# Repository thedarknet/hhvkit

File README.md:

hhvkit
======

DefCon 23 Hardware Hacking Village Learn To Solder Kit, by:
- Smitty, mark@halibut.com (concept, crypto, and firmware (2014))
- Krux, krux@thcnet.net (hardware)
- Cmdc0de, comc0dez@gmail.com (firmware (2015))

These are the files needed to build the firmware for the DefCon DarkNet
ID Badge that was sold as the Hardware Hacking Village's Learn To Solder
kit at DefCon 23 in 2015.

If you checkout the repo into your Arduino folder, it should just build
on Arduino v1.6.4.  

It creates the following directories:

DCDarkNet/Firmware/
- Contains the code.

DCDarkNet/Firmware/build/
- The automated build/burn system used to program over 300 chips in 
  just a couple hours. (ZIF socket not included. Some assembly required.)

libraries/IRSerial2014/
- A modified version of SoftwareSerial from Arduino 1.0 (don't know if 
  it's changed at all in 1.5) to allow for independent inverted logic
  on the Rx and Tx lines (so the idle state isn't HIGH on the IR LED
  and burn through battery), and to perform 38kHz modulation for the IR.

libraries/UsbKeyboard/
- A version of vusb-for-arduino [1] modified so it doesn't instantiate
  the USB object in the .h file and therefore immeidately upon startup.
  Instead, you instantiate the object whenever you want it and can
  delete it when you're done.
  [1] https://code.google.com/p/vusb-for-arduino/

libraries/DarkNetDisplay
- Modified version of the adafruit gfx and ssd_1306 libraries to work with our 
  darknet badge display
	https://github.com/adafruit/Adafruit-GFX-Library
	https://github.com/adafruit/Adafruit_SSD1306

Building and Burning
======

All the following commands are run inside DCDarkNet/Firmware/build/
This section is really only relevant if you are burning this code into
a whole bunch of chips.  If you're just burning your own chip, or are
playing around with different code, you're better off just using the 
Arduino IDE to program the board directly with an FTDI cable.

Preparation: GUIDs and private keys
======
The code is programmed to FLASH, but there are a few things needed in
EEPROM before the badge is functional.  If you have a chip from us, it
was already programmed with your GUID and private key, which will persist
through a re-flash.  But if you have a new chip, you'll need to program
your GUID and private key into the chip.

We don't currently (2015-08-2) have a way to generate new GUIDs and 
keys for you, nor to take in GUIDs and keys from you to put into the DB.
So you're welcome to play with this code and use it for other things, 
but unless you got a chip from us at DefCon, you won't be able to 
use your code on the live DarkNet site (https://dcdark.net.)

If you're building a whole new name space and don't need to interact 
with the DefCon DarkNet Daemon, you can generate your own DB of random
GUIDs and private keys using the build/buildDB.pl script, and redirecting
the output to a file called DB.  This doesn't actually do anything with 
the chip, it just generates random numbers and formats them correctly.

build$ ./buildDB.pl > DB

Preparation: Program
=======
All the source code is compiled down into a .hex file by Arduino. Those
who do more microcontroller work than I do can build this by hand.  I'm 
lazy and let Arduino do all the drudgery for me.

Go to preferences and enable "verbose output of the build process" or
whatever it's called.  This will make Arduino NOT delete the temporary
build directories it creates in /tmp.  Then build the code with Ctrl-R.
That will burn into /tmp/build[some number].tmp/   Find the most recent
build directory (the one that was likely just created or updated), and
copy Firmware.cpp.hex to your build/ directory:

build$ cp /tmp/build[some number].tmp/Firmware.cpp.hex .

You will have to do this EVERY TIME you build.

Burning Chips
=======
The burn-bootloader.sh script assumes you have a USBtinyISP [2].  You'll
need to modify the avr-dude command if you have a different ISP.
[2] http://www.adafruit.com/product/46

Connect the USBtinyISP to the ICSP header on your board and run:

build$ ./burn-bootloader.sh

Congrats!  Your badge is now an Arduino!  It can be programmed through
the FTDI header as if it were an Uno.

But to make it a DarkNet ID Badge, it needs the GUID and private key in 
EEPROM, and the program in flash.

The burn-eeprom.sh script takes a GUID on the command line, pulls it 
and it's associated key from the "DB" file generated above, formats
them into a .hex file that avr-dude can burn to EEPROM, and burns it.
Again, you'll need the USBtinyISP plugged into the ICSP header:

build$ ./burn-eeprom.sh GUIDGUID

After those two are done, the program can be written to flash using
the FTDI serial console cable (it's much faster than using the ICSP.)
burn-flash.sh takes the local file Firmware.cpp.hex you copied 
above.

build$ ./burn-flash.sh

Automating the Build
======
I wasn't about to run these three commands manually for 350 chips, so 
I wrote run.pl which pulls all the GUIDs from DB and cycles through 
them.  If all is happy and working, you can just run.pl, hit enter to
program a chip, swap the chip in the programming rig, hit enter again, 
lather, rinse, repeat.  It takes care of all the iteration on GUID,
as well as allows you to <N>ext and <P>rev through the DB list in case
a burn goes awry and needs to be redone.

build$ ./run.pl

BOM and Assembly Instructions
======

The Bill of Materials is located here:

https://www.mouser.com/ProjectManager/ProjectDetail.aspx?AccessID=6bc2d848d8

Assembly Instructions are located here:

- https://dcdark.net/2015/hhv-badge/
- https://dcdark.net/2015/hhv-display/

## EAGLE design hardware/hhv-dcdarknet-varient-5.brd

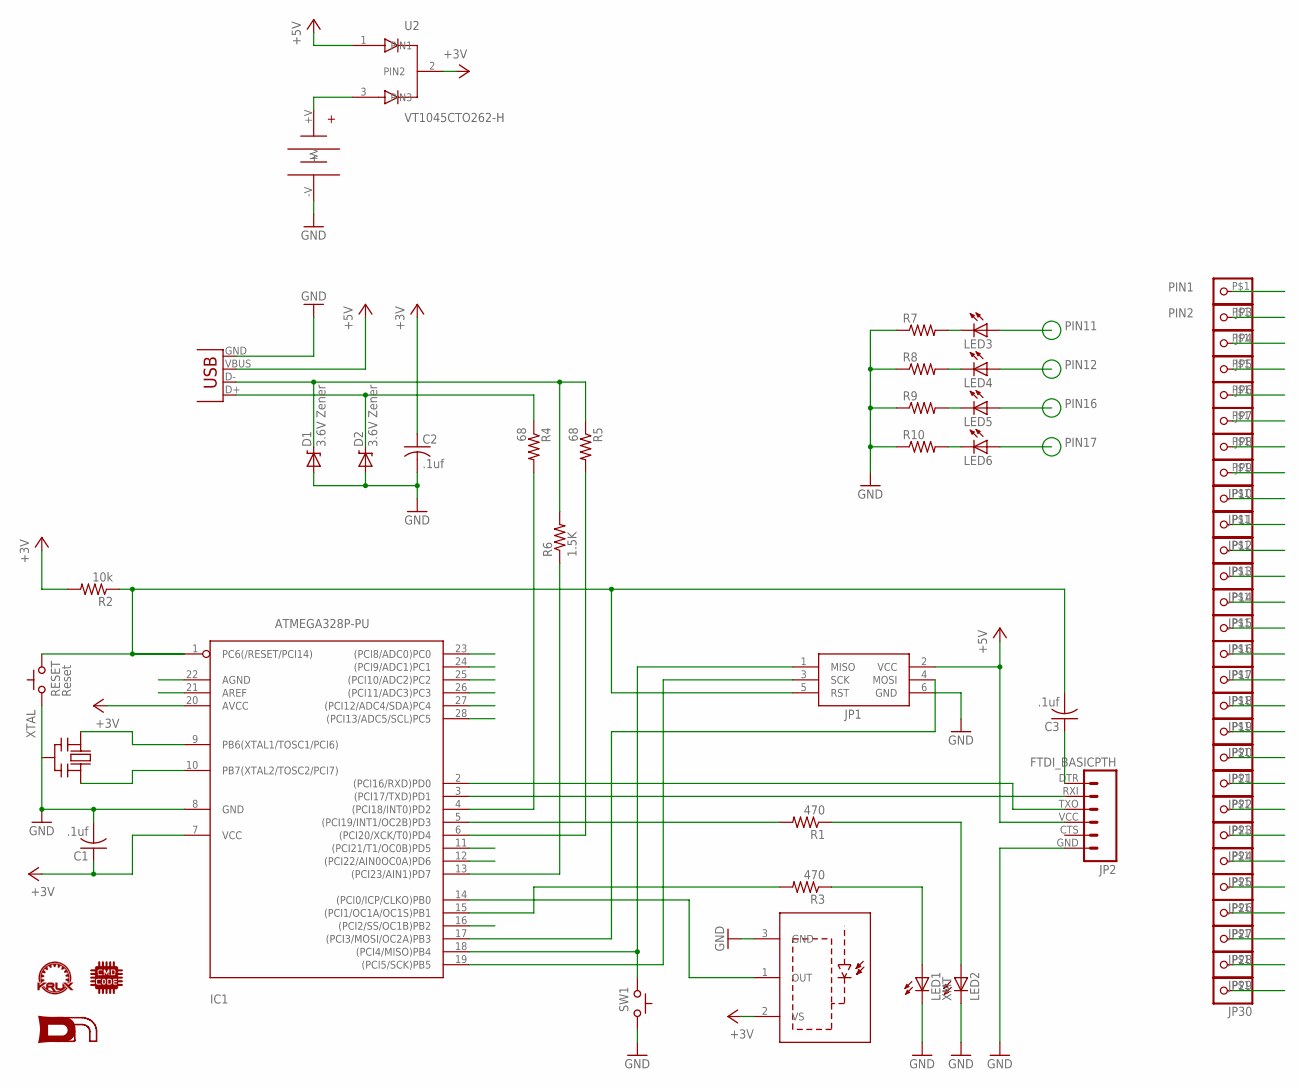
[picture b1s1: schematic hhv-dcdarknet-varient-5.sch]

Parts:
C1, C2, C3: .1uf; C025-030X050
D1, D2: 3.6V Zener; DIODE-ZENER
IC1: ATMEGA328P-PU; DIL28-3
JP1: JP1; AVRISP
JP2: FTDI_BASICPTH; FTDI_BASIC
JP3, JP4, JP5, JP6, JP7, JP8, JP9, JP10, JP11, JP12, JP13, JP14, JP15, JP16, JP17, JP18, JP19, JP20, JP21, JP22, JP23, JP24, JP25: PINHD-1X11X1_SQUARE; 1X1-SMALL_CUT
JP26, JP27, JP28, JP29, JP30: PINHD-1X11X1-SMALL; 1X1-SMALL
LED1: XMT; LED5MM-FLAT
LED2: LED5MM-FLAT
LED3, LED4, LED5, LED6: LED1206; LED-1206
R1, R3: 470; AXIAL-0.3
R2: 10k; AXIAL-0.3
R4, R5: 68; AXIAL-0.3
R6: 1.5K; AXIAL-0.3
R7, R8, R9, R10: RESISTOR1206; 1206
RESET: Reset; TACTILE-2PIN
SW1: SWITCH_TACTILETACTILE-2PIN; TACTILE-2PIN
U1: RCV; IR-MODULE
U2: VT1045CTO262-H; TO262-H
U$1: DN_LOGO
U$2: CMDC0DE_LOGO; CMDC0DE
U$3: KRUX_LOGO
U$5: 12BH423-GR3-CELL_NOBORDER; 3-AAA-CELL_NOBORDER
X2: USB; USB-B-PTH
XTAL: CERMOSCILL-THM; CERM_OSC

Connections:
+3V3: C1.1, C2.1, IC1.7 (VCC), IC1.20 (AVCC), JP9.P$1, JP22.P$1, R2.P$2 (2), U1.2 (VS), U2.2 (PIN2)
+5V: JP1.2 (VCC), JP2.VCC (4), U2.1 (PIN1), X2.VBUS
GND: C1.2, C2.2, D1.P$2 (A), D2.P$2 (A), IC1.8 (GND), JP1.6 (GND), JP2.GND (6), JP10.P$1, LED1.K (C), LED2.K (C), R7.1, R8.1, R9.1, R10.1, RESET.P$2 (C), SW1.P$1 (A), U1.3 (GND), U$5.-V, X2.GND, XTAL.P$2 (GND)
unnamed: C3.1, JP2.DTR (1)
unnamed: LED3.C, R7.2
unnamed: LED4.C, R8.2
unnamed: LED5.C, R9.2
unnamed: LED6.C, R10.2
unnamed: LED1.A, R3.P$1 (1)
unnamed: LED2.A, R1.P$1 (1)
unnamed: D2.P$1 (C), R4.P$1 (1), X2.D+
unnamed: U2.3 (PIN3), U$5.+V
PIN1: C3.2, IC1.1 (PC6(/RESET/PCI14)), JP1.5 (RST), JP3.P$1, R2.P$1 (1), RESET.P$1 (A)
PIN2: IC1.2 ((PCI16/RXD)PD0), JP2.TXO (3), JP4.P$1
PIN3: IC1.3 ((PCI17/TXD)PD1), JP2.RXI (2), JP5.P$1
PIN4: IC1.4 ((PCI18/INT0)PD2), JP6.P$1, R4.P$2 (2)
PIN5: IC1.5 ((PCI19/INT1/OC2B)PD3), JP7.P$1, R1.P$2 (2)
PIN6: IC1.6 ((PCI20/XCK/T0)PD4), JP8.P$1, R5.P$2 (2)
PIN9: IC1.9 (PB6(XTAL1/TOSC1/PCI6)), JP11.P$1, XTAL.P$1 (IN)
PIN10: IC1.10 (PB7(XTAL2/TOSC2/PCI7)), JP12.P$1, XTAL.P$3 (OUT)
PIN11: IC1.11 ((PCI21/T1/OC0B)PD5), JP13.P$1, LED3.A
PIN12: IC1.12 ((PCI22/AIN0OC0A)PD6), JP14.P$1, LED4.A
PIN13: IC1.13 ((PCI23/AIN1)PD7), JP15.P$1, R6.P$1 (1)
PIN14: IC1.14 ((PCI0/ICP/CLKO)PB0), JP16.P$1, U1.1 (OUT)
PIN15: IC1.15 ((PCI1/OC1A/OC1S)PB1), JP17.P$1, R3.P$2 (2)
PIN16: IC1.16 ((PCI2/SS/OC1B)PB2), JP18.P$1, LED5.A
PIN17: IC1.17 ((PCI3/MOSI/OC2A)PB3), JP1.4 (MOSI), JP19.P$1, LED6.A
PIN18: IC1.18 ((PCI4/MISO)PB4), JP1.1 (MISO), JP20.P$1, SW1.P$2 (C)
PIN19: IC1.19 ((PCI5/SCK)PB5), JP1.3 (SCK), JP21.P$1
PIN21: IC1.21 (AREF), JP23.P$1
PIN22: IC1.22 (AGND), JP24.P$1
PIN23: IC1.23 ((PCI8/ADC0)PC0), JP25.P$1
PIN24: IC1.24 ((PCI9/ADC1)PC1), JP26.P$1
PIN25: IC1.25 ((PCI10/ADC2)PC2), JP27.P$1
PIN26: IC1.26 ((PCI11/ADC3)PC3), JP28.P$1
PIN27: IC1.27 ((PCI12/ADC4/SDA)PC4), JP29.P$1
PIN28: IC1.28 ((PCI13/ADC5/SCL)PC5), JP30.P$1
USB: D1.P$1 (C), R5.P$1 (1), R6.P$2 (2), X2.D-

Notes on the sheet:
PIN11
PIN12
PIN16
PIN17

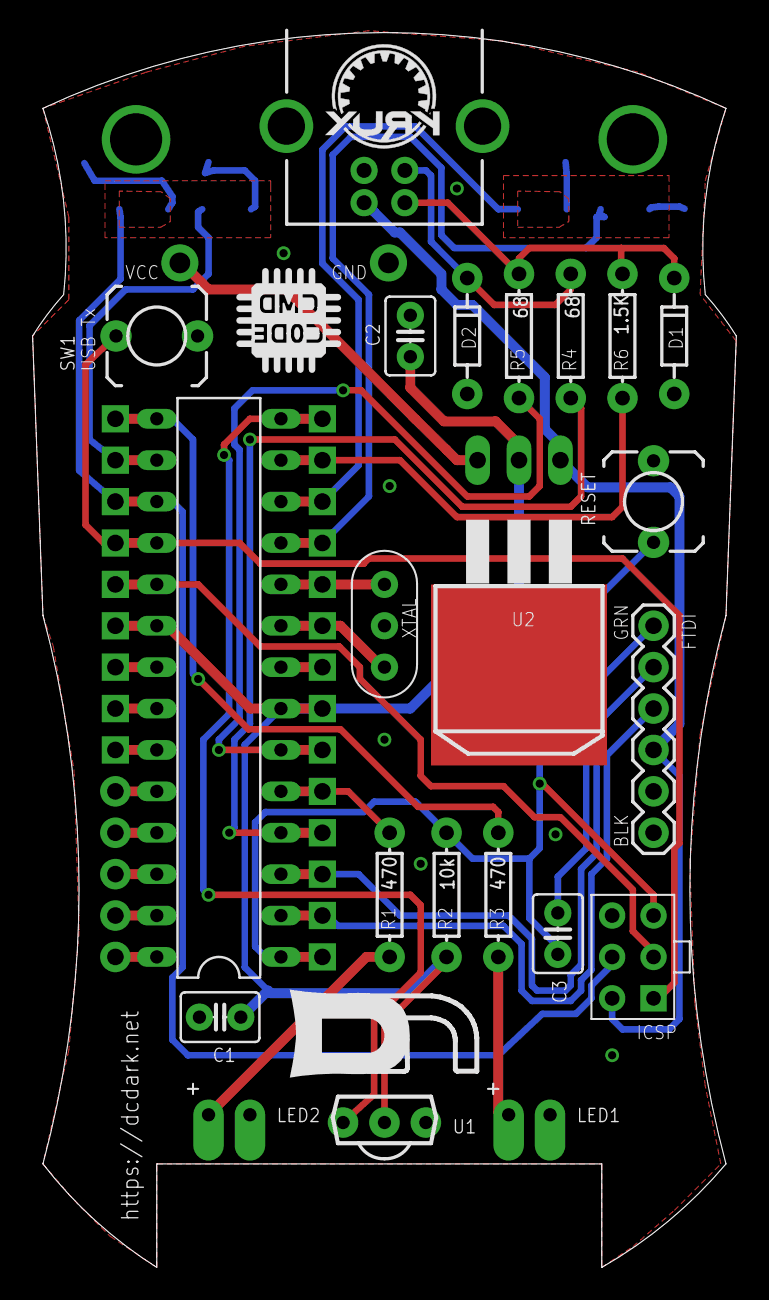
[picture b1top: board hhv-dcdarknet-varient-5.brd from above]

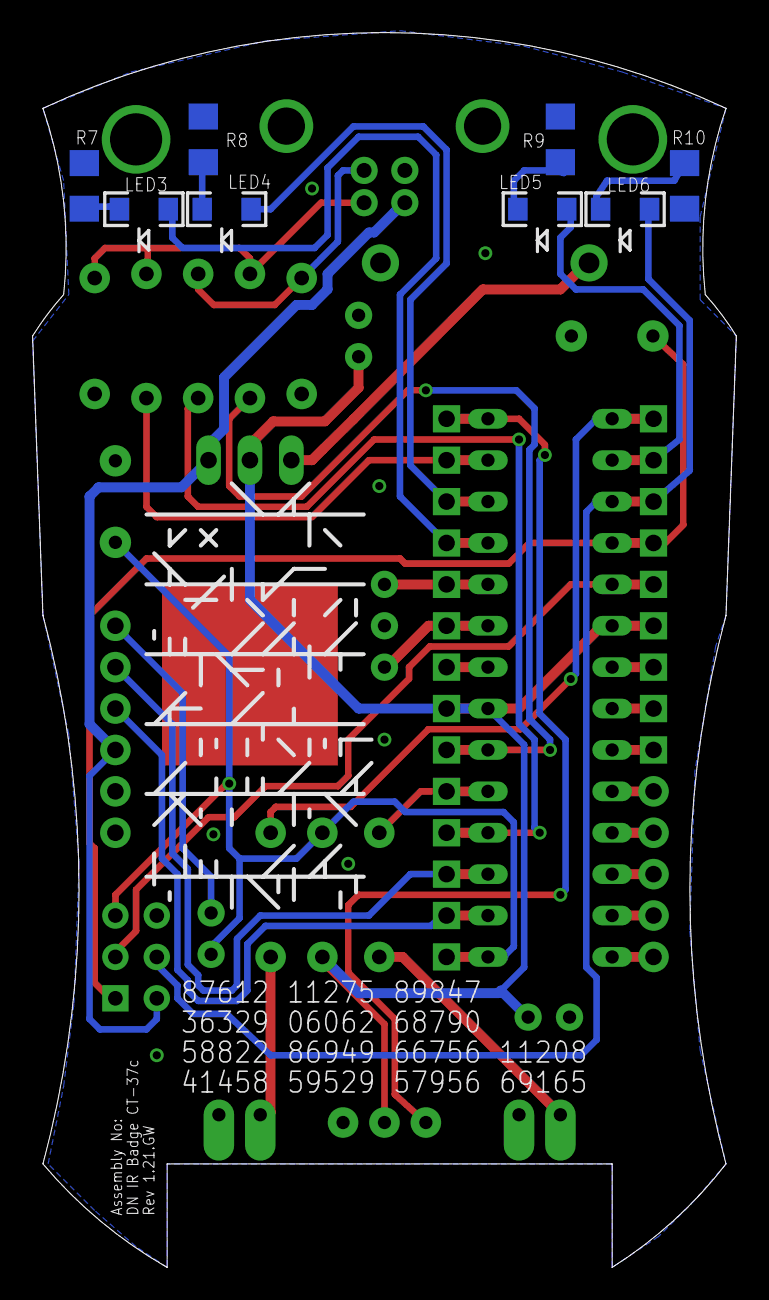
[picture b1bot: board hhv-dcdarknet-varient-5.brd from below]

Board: 2 copper layers, 43.2 x 75.8 mm, 62 parts (10 on the bottom side), 38 nets.

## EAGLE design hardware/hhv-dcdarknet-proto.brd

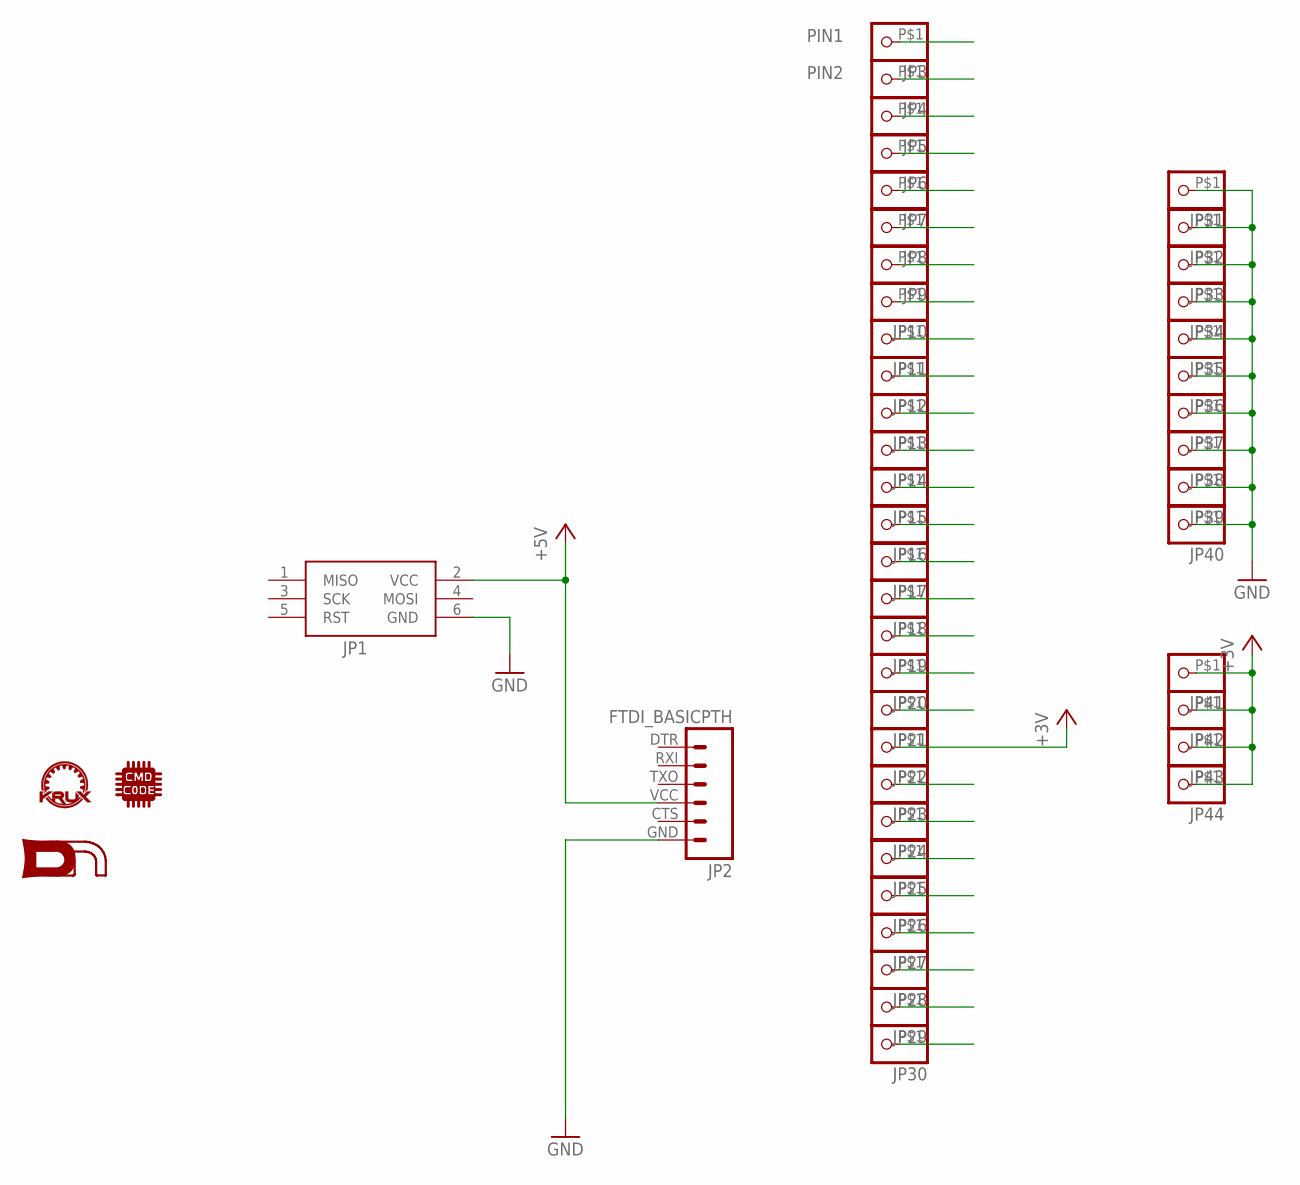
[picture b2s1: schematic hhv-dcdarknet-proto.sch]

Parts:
JP1: JP1; AVRISP
JP2: FTDI_BASICPTH; FTDI_BASIC
JP3, JP4, JP5, JP6, JP7, JP8, JP9, JP10, JP11, JP12, JP13, JP14, JP15, JP16, JP17, JP18, JP19, JP20, JP21, JP22, JP23, JP24, JP25, JP26, JP27, JP28, JP29, JP30, JP31, JP32, JP33, JP34, JP35, JP36, JP37, JP38, JP39, JP40, JP41, JP42, JP43, JP44: PINHD-1X11X1_SQUARE; 1X1-SMALL_CUT
U$1: KRUX_LOGO
U$2: DN_LOGO
U$3: CMDC0DE_LOGO; CMDC0DE

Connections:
+3V3: JP9.P$1, JP22.P$1, JP41.P$1, JP42.P$1, JP43.P$1, JP44.P$1
+5V: JP1.2 (VCC), JP2.VCC (4)
GND: JP1.6 (GND), JP2.GND (6), JP10.P$1, JP31.P$1, JP32.P$1, JP33.P$1, JP34.P$1, JP35.P$1, JP36.P$1, JP37.P$1, JP38.P$1, JP39.P$1, JP40.P$1
PIN1: JP3.P$1
PIN2: JP4.P$1
PIN3: JP5.P$1
PIN4: JP6.P$1
PIN5: JP7.P$1
PIN6: JP8.P$1
PIN9: JP11.P$1
PIN10: JP12.P$1
PIN11: JP13.P$1
PIN12: JP14.P$1
PIN13: JP15.P$1
PIN14: JP16.P$1
PIN15: JP17.P$1
PIN16: JP18.P$1
PIN17: JP19.P$1
PIN18: JP20.P$1
PIN19: JP21.P$1
PIN21: JP23.P$1
PIN22: JP24.P$1
PIN23: JP25.P$1
PIN24: JP26.P$1
PIN25: JP27.P$1
PIN26: JP28.P$1
PIN27: JP29.P$1
PIN28: JP30.P$1

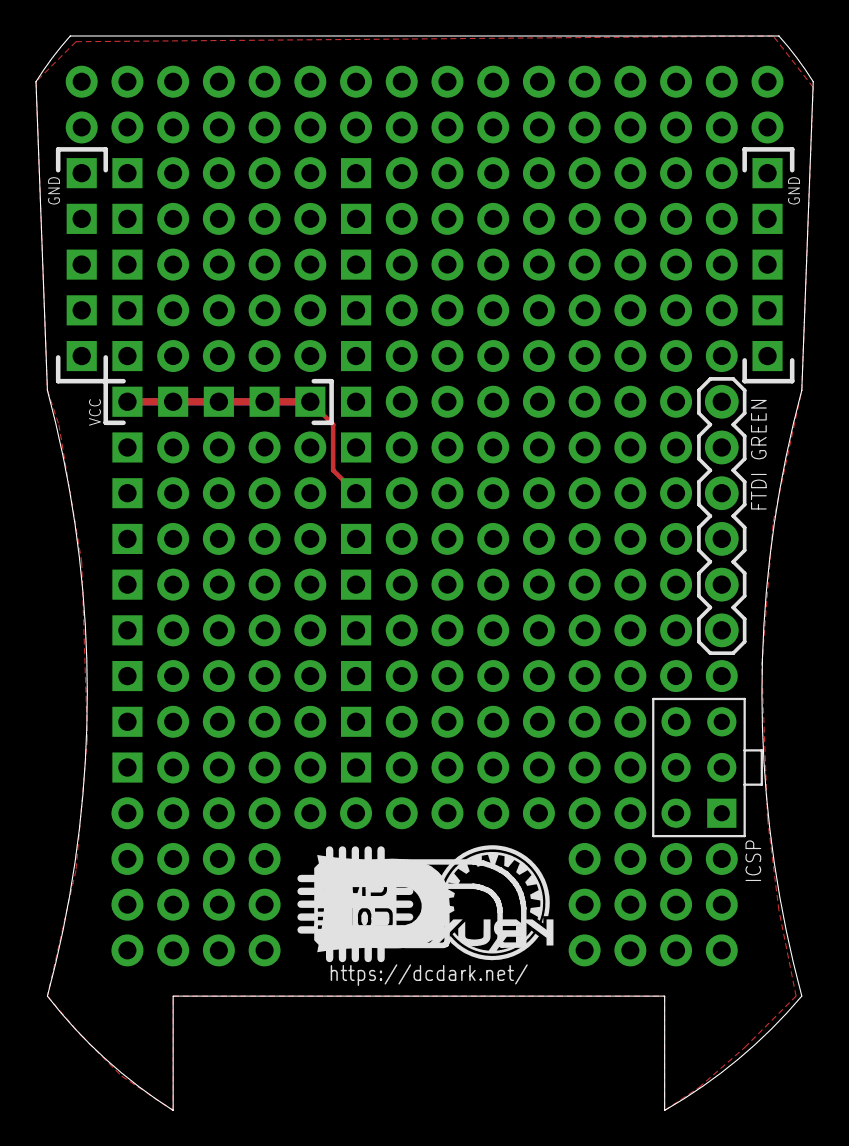
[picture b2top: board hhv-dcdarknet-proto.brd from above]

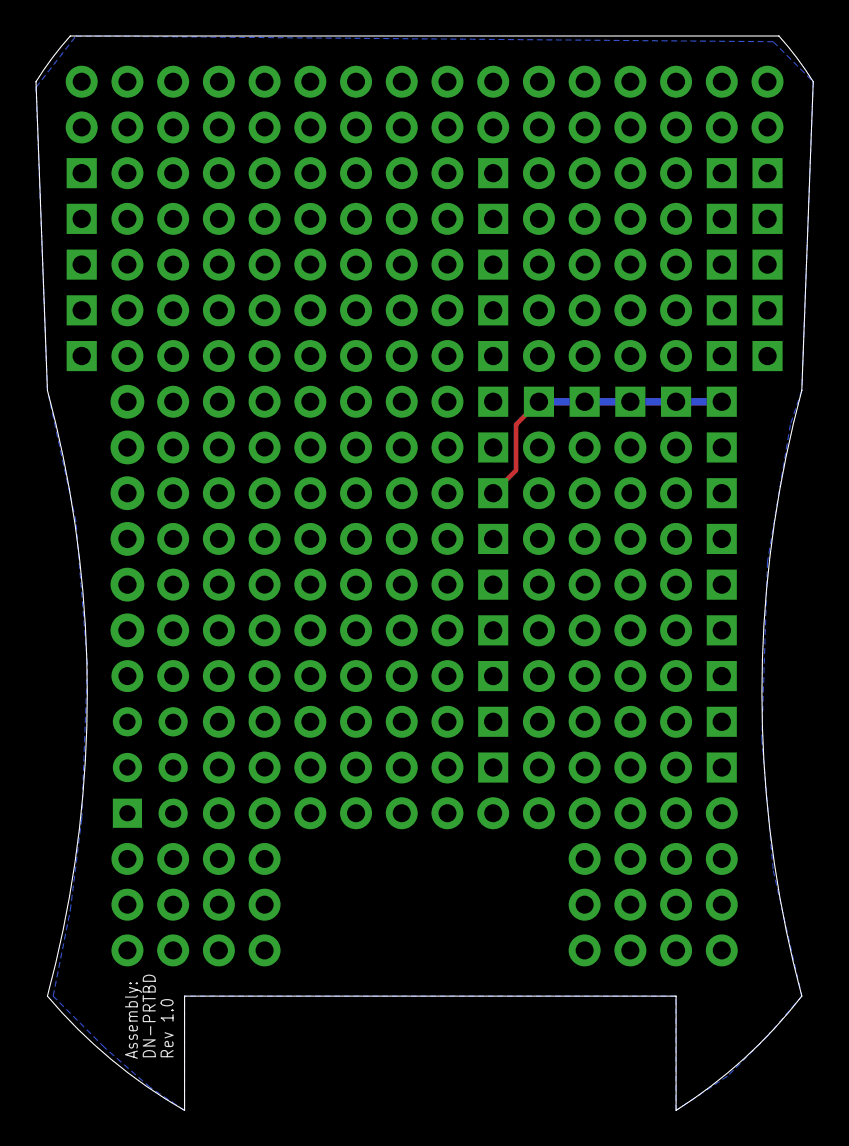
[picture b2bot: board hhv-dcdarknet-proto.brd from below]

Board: 2 copper layers, 43.2 x 59.7 mm, 47 parts (2 on the bottom side), 3 nets.

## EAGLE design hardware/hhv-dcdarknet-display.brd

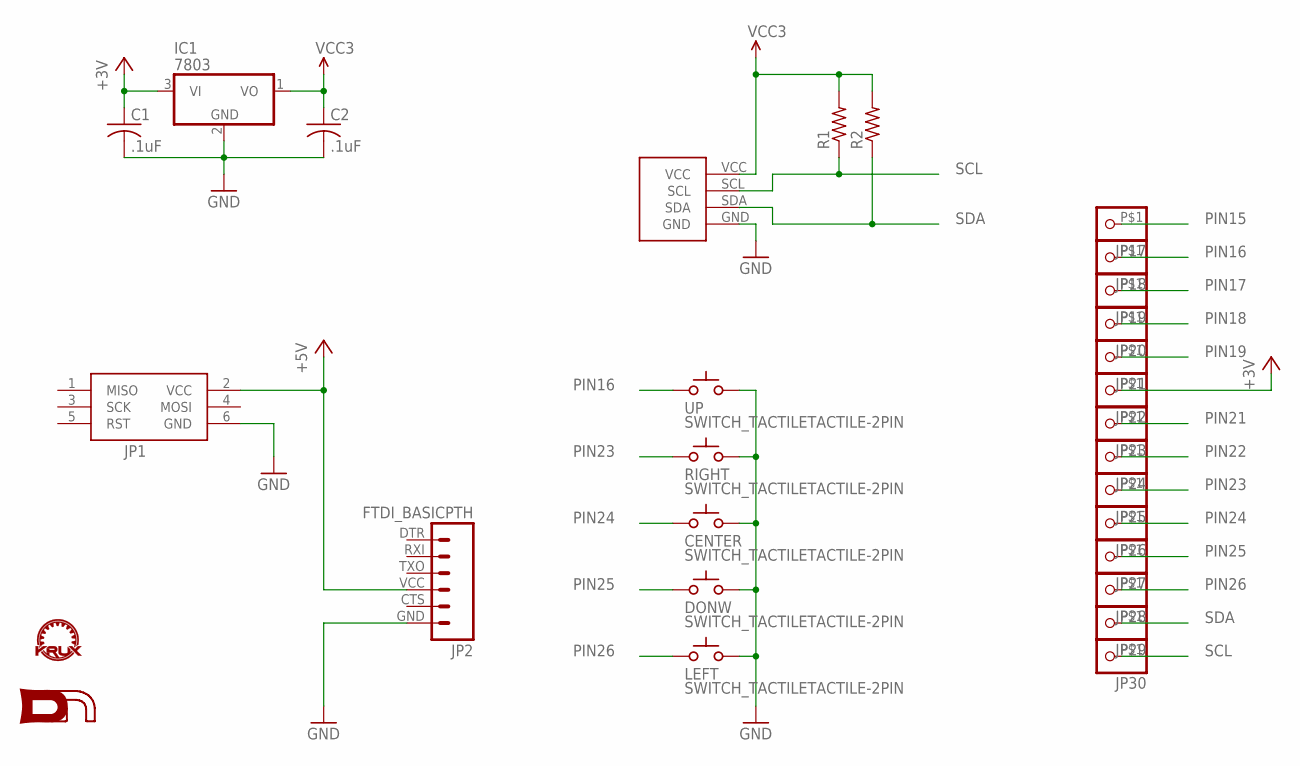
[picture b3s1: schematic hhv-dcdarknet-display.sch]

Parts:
C1, C2: .1uF; C025-030X050
CENTER: SWITCH_TACTILETACTILE-2PIN; TACTILE-2PIN
DONW: SWITCH_TACTILETACTILE-2PIN; TACTILE-2PIN
IC1: 7803; TO92
JP1: JP1; AVRISP
JP2: FTDI_BASICPTH; FTDI_BASIC
JP17, JP18, JP19, JP20, JP21, JP22, JP23, JP24, JP25, JP26, JP27, JP28, JP29, JP30: PINHD-1X11X1_SQUARE; 1X1-SMALL_CUT
LEFT: SWITCH_TACTILETACTILE-2PIN; TACTILE-2PIN
R1, R2: R-US_0204/5; 0204/5
RIGHT: SWITCH_TACTILETACTILE-2PIN; TACTILE-2PIN
U$1: KRUX_LOGO
U$2: DN_LOGO
U$3: I2C_0.96_OLEDOLED; I2C_0.96_OLED
UP: SWITCH_TACTILETACTILE-2PIN; TACTILE-2PIN

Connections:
+3V3: C1.1, IC1.3 (VI), JP22.P$1
+5V: JP1.2 (VCC), JP2.VCC (4)
GND: C1.2, C2.2, CENTER.P$1 (A), DONW.P$1 (A), IC1.2 (GND), JP1.6 (GND), JP2.GND (6), LEFT.P$1 (A), RIGHT.P$1 (A), U$3.GND, UP.P$1 (A)
PIN15: JP17.P$1
PIN16: JP18.P$1, UP.P$2 (C)
PIN17: JP19.P$1
PIN18: JP20.P$1
PIN19: JP21.P$1
PIN21: JP23.P$1
PIN22: JP24.P$1
PIN23: JP25.P$1, RIGHT.P$2 (C)
PIN24: CENTER.P$2 (C), JP26.P$1
PIN25: DONW.P$2 (C), JP27.P$1
PIN26: JP28.P$1, LEFT.P$2 (C)
PIN27: JP29.P$1, R2.1, U$3.SDA
PIN28: JP30.P$1, R1.1, U$3.SCL
VCC3: C2.1, IC1.1 (VO), R1.2, R2.2, U$3.VCC

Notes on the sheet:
SCL
SDA
PIN26
PIN25
PIN24
PIN23
PIN22
PIN21
PIN19
PIN18
PIN17
PIN16
PIN15

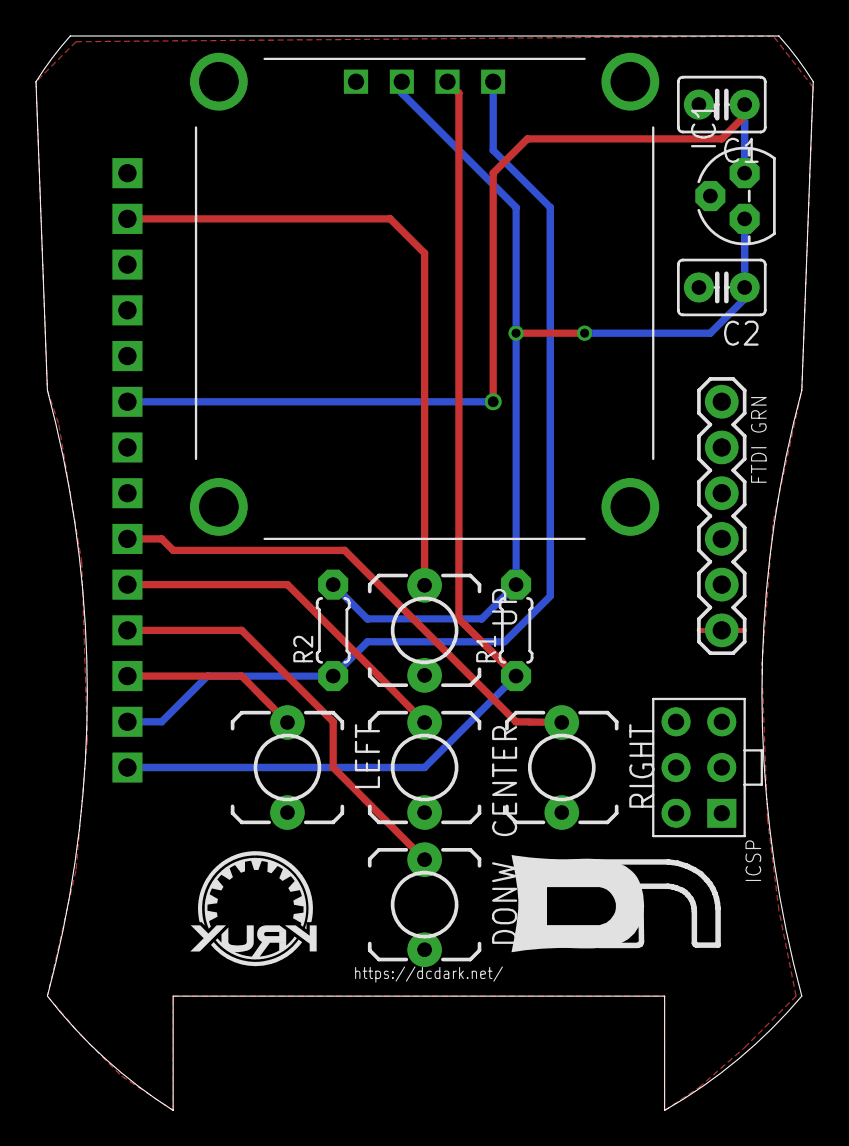
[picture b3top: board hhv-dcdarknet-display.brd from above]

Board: 2 copper layers, 43.2 x 59.7 mm, 29 parts (1 on the bottom side), 11 nets.

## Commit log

2014-08-11 Initial check-in after DefCon 22. First public release.
2014-08-11 Added schematic and board files. (Eagle format.)
2014-08-11 Making README.md look better when viewed on github
2014-08-11 Oops, missed a reformat
2015-03-05 private
2015-03-09 Created 2015 branch Renamed IR_Quest_2014 to Firmware added calibration on reset to usb For me this took an old netbook from never working with the badget to 'sort of working', I can get up to 3 star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
    Next check in I plan to remove tv_b_gone check in
    Next check in I will try the continueous calibration (if possible, it only works if D+ is connected to the interrupt and I have
2015-03-30 removing tv-b-gone and putting back the osc-cal
2015-04-06 Adding compiled binary for badge
2015-04-06 clean up for firmware and remove an unneeded comment for the usb config
2015-05-08 updated config data to say 2015 Added defines so we can turn off and on serial debugging quickly Updated USB Key board test to work with calibration code
2015-05-11 Update hhv-dcdarknet.brd
    Updated version for DC23. Adjustments on layout and increased pad sizes and spacing. Silk screen has not been updated yet.
2015-05-11 Update hhv-dcdarknet.sch
    Updated board for DC23.
2015-05-11 hhv-dcdarknet-display.brd
    Display daughter board addon
2015-05-11 hhv-dcdarknet-display.sch
    Display daughter board schematic
2015-05-30 issue 3: Functionally complete
    Needed to be Done done done:
    1) Current the password is set to cmdc0de
    Will this work for the story? If not what should it be
    2) Current the question is: What is the answer to all things?
    You should know the answer
2015-05-30 Add udev rules file for avrispmkII
2015-05-30 Add python module for controlling Sparkfun Serial LCD
2015-05-30 Adding some notes about installation on BeagleBone
2015-05-30 removing unneeded file
2015-05-30 Adding what I have of the updater.py
2015-05-30 Adding support for avr dragon isp
2015-05-30 Added support for AVR dragon and FTDI/arduino NOTE: EEPROM doesn't seem to work with arduino mode
2015-05-30 Adding misc notes and BeagleBone UART setup script
2015-06-01 initial check in for display board, just libraries and some minor code refactoring As well as test code for display
2015-06-03 Return avrdude process return/exit code Only add 2 second delay if we're using avrdragon
2015-06-03 Added 'autodetect' feature that checks all programmers to see if a device is connected. Once it finds one, it proceeds
2015-06-03 Cleanup error message and make sure we return 1 when unsuccessfully exiting
2015-06-03 Make sure we return a filename with the readFlash function
2015-06-03 Add 'modes' to have more control of what the script actually does
2015-06-03 Adding last years files
2015-06-03 make dragonWait a function since we might have to use it more often
2015-06-04 Adding modeFlashBootloader which works if the AVR is on a badge (avr dragon doesn't have oscillator...)
2015-06-04 Reduce memory by removing unused IR speeds
2015-06-06 These changes save 116 bytes from program memory at the expense of 28 bytes in dynamic memory
2015-06-29 DarkNetDisplay Library up and running
2015-06-29 display is now working 100% but I'm out of global memory again. Going to need to write a progmem version of sendmorsestr().
2015-06-29 more space freed up by creating a sendToMorseStr that takes a flash string
2015-07-05 issue 15 finally complete!
2015-07-05 removed debug code
2015-07-06 removing unneeded libraries
2015-07-06 issue 17 complete
2015-07-09 cool display code complete. Runs John Conway's game of life
2015-07-11 added back the backlight led ramps reduced global memory by nearly another 100 bytes
2015-07-11 now using the darknet logo for display 'splash screen'
2015-07-11 increased time on splash screen
2015-07-12 adding more debugging back
2015-07-13 clean up
2015-07-18 serial port epic updated so that you no longer answer the question 'what is the answer to all things'? and the password was chaged from cmdc0de to JOSHUA
    Now if your firmware is burned with MAKE_ME_A_CONTEST_RUNNER defined to anything but 0 you can put your badge into mode 7 and
    read display for instructions on how to complete the 6 part silk screen crypto for the agent. The agent will get a special GUID sent to them
    that will be used for yet another badge specific validation string for the server
2015-07-18 commented out unneeded code
2015-07-19 Split off most of the avr programming functions onto separate file. Should help getting standalone (autorun) version working
2015-07-19 Make sure write progress works
2015-07-19 forgot to update these variables
2015-07-19 adding autoupdate script that waits for pushbutton input, then flashes the badge (with LCD updates!)
2015-07-26 Check that there's an FTDI device plugged in
2015-07-26 Adding some service things and updating BBSetup notes
2015-08-03 added debug code to help with end points
2015-08-03 ensure that when we print out the validate code that a number less than 16 is still 2 characters in the hexstring
2015-08-04 up the ir serial buffer back to 32 bytes 14 is too tight
2015-08-04 last crypto quest complete
2015-08-04 more serial port debugging info...proved out last part of the crypto badge works
2015-08-04 tweaked timeing on display epic fixed over read on serial
2015-08-05 fixed bad serial output
2015-08-06 set seed for life to the bad secret key!
2015-08-06 fixed a serial output bug
2015-08-14 Updated Eagle files for the 2015 boards.
2015-08-14 removed bottom lines

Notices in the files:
parts and their libraries:
SparkFun: Licensing: CC v3.0 Share-Alike You are welcome to use this library for commercial purposes.
